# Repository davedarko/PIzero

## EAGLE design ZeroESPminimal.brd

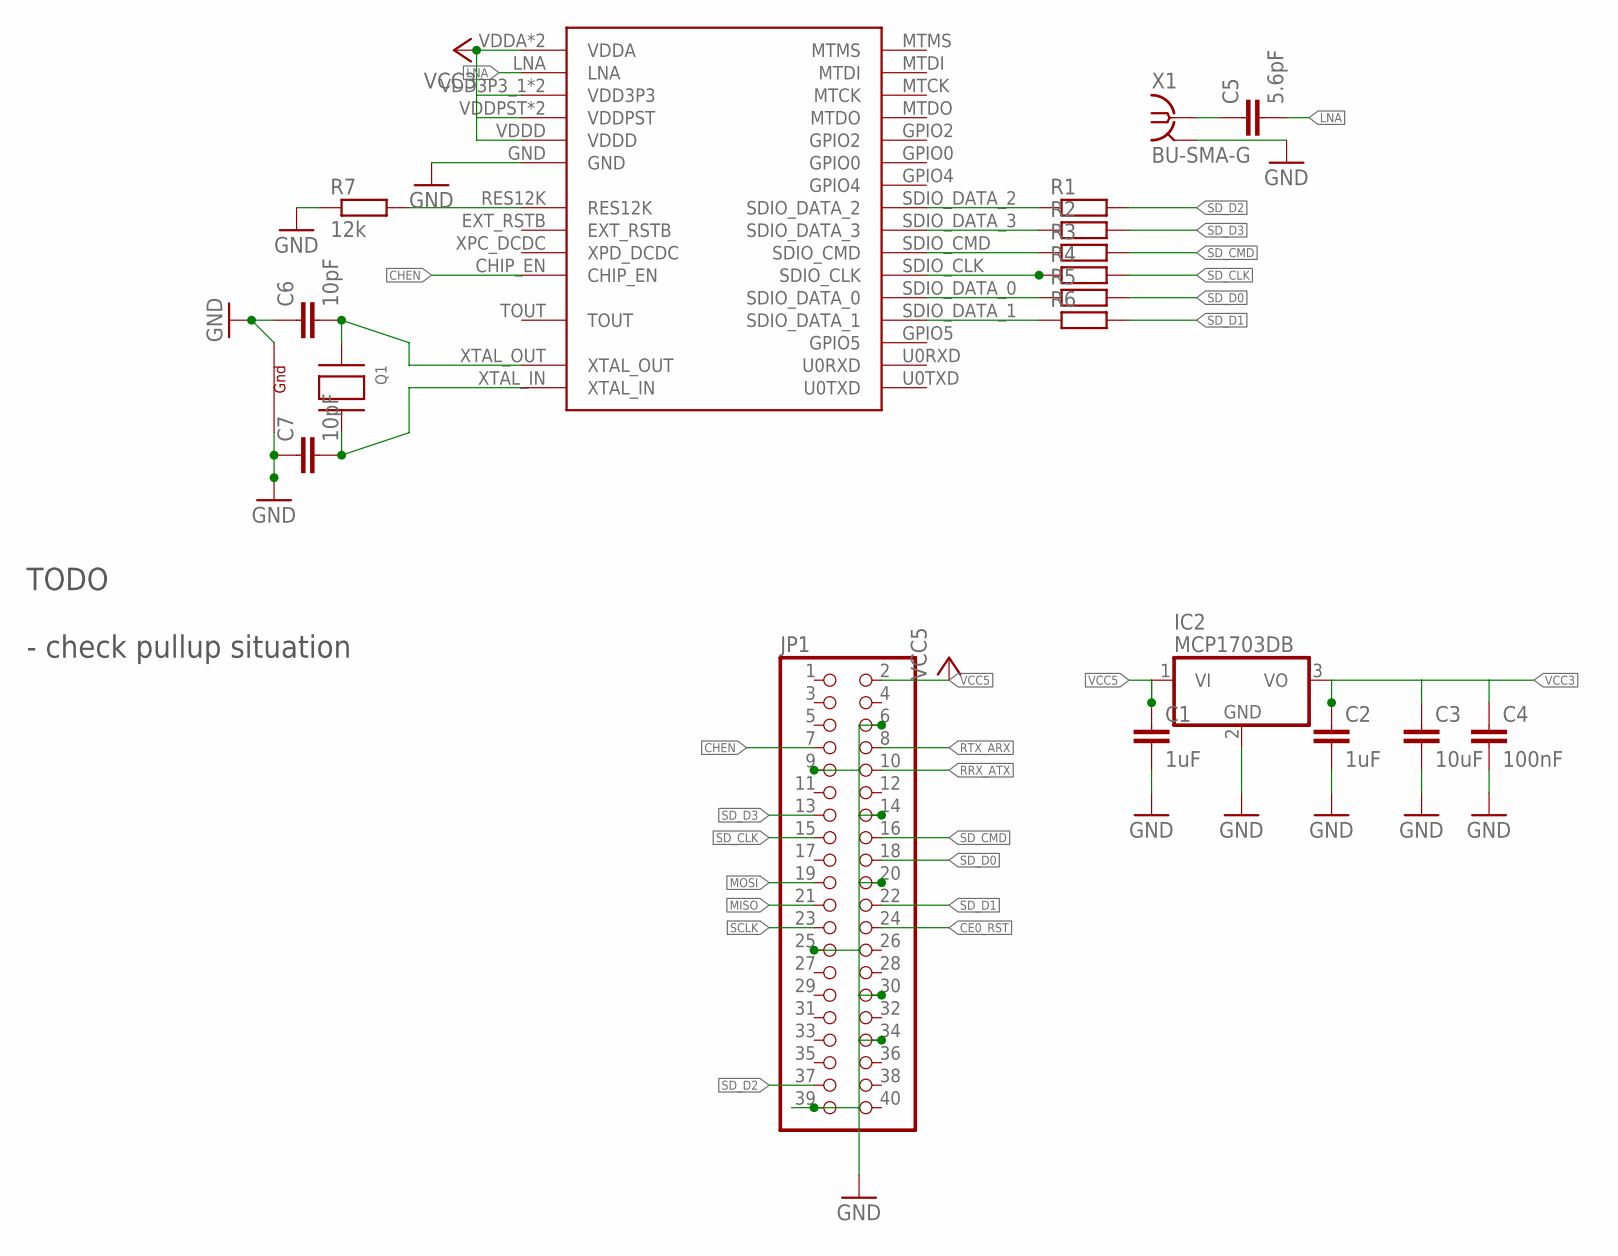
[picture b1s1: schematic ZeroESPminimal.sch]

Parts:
C1, C2: 1uF; C1206
C3: 10uF; C1206
C4: 100nF; C1206
C5: 5.6pF; C0402
C6, C7: 10pF; C0402
IC2: MCP1703DB; SOT223
JP1: PINHD-2X20; 2X20
Q1: XTAL-4-3225; NX3225
R1, R2, R3, R4, R5, R6: R-EU_R0402; R0402
R7: 12k; R0402
U$3: ESP8266EX
X1: BU-SMA-G

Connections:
$N22: R3.1, U$3.SDIO_CMD
$N23: R5.1, U$3.SDIO_DATA_0
$N24: R6.1, U$3.SDIO_DATA_1
CE0_RST: JP1.24
CHEN: JP1.7, U$3.CHIP_EN
GND: C1.2, C2.2, C3.2, C4.2, C6.1, C7.1, IC2.2 (GND), JP1.6, JP1.9, JP1.14, JP1.20, JP1.25, JP1.30, JP1.34, JP1.39, Q1.2 (G2), Q1.4 (G1), R7.1, U$3.GND, X1.2, X1.3 (2), X1.4 (2), X1.5 (2)
LNA: C5.2, U$3.LNA
MISO: JP1.21
MOSI: JP1.19
unnamed: R1.1, U$3.SDIO_DATA_2
unnamed: R2.1, U$3.SDIO_DATA_3
unnamed: C5.1, X1.1
unnamed: R4.1, U$3.SDIO_CLK
unnamed: R7.2, U$3.RES12K
unnamed: C6.2, Q1.1 (X1), U$3.XTAL_OUT
unnamed: C7.2, Q1.3 (X2), U$3.XTAL_IN
RRX_ATX: JP1.10
RTX_ARX: JP1.8
SCLK: JP1.23
SD_CLK: JP1.15, R4.2
SD_CMD: JP1.16, R3.2
SD_D0: JP1.18, R5.2
SD_D1: JP1.22, R6.2
SD_D2: JP1.37, R1.2
SD_D3: JP1.13, R2.2
VCC3: C2.1, C3.1, C4.1, IC2.3 (VO), U$3.VDD3P3_1 (VDD3P3), U$3.VDD3P3_2 (VDD3P3), U$3.VDDA, U$3.VDDA_2 (VDDA), U$3.VDDD, U$3.VDDPST, U$3.VDDPST_2 (VDDPST)
VCC5: C1.1, IC2.1 (VI), JP1.2

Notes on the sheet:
TODO - check pullup situation

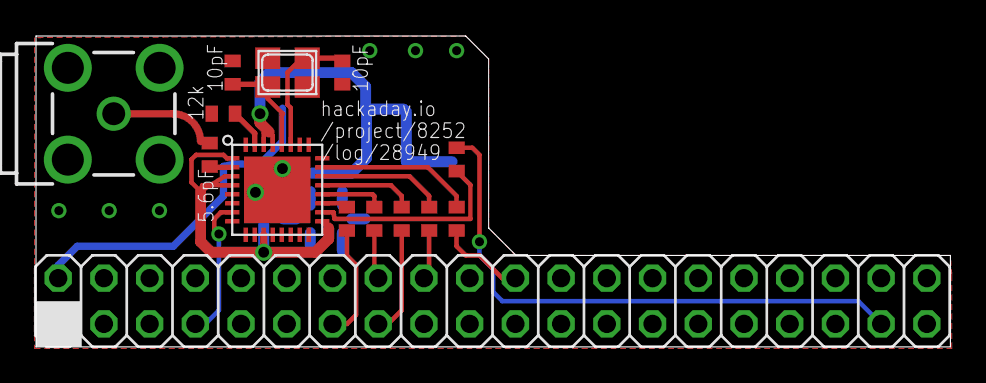
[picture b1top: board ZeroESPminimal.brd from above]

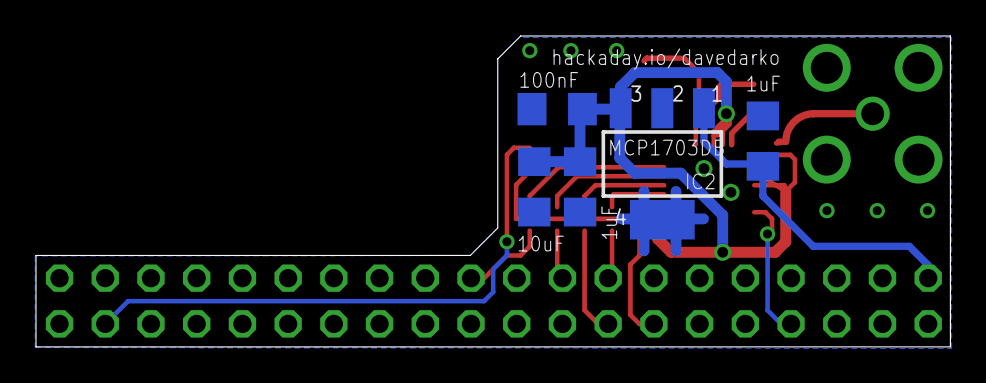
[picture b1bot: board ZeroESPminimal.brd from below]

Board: 2 copper layers, 50.8 x 17.3 mm, 19 parts (5 on the bottom side), 21 nets.

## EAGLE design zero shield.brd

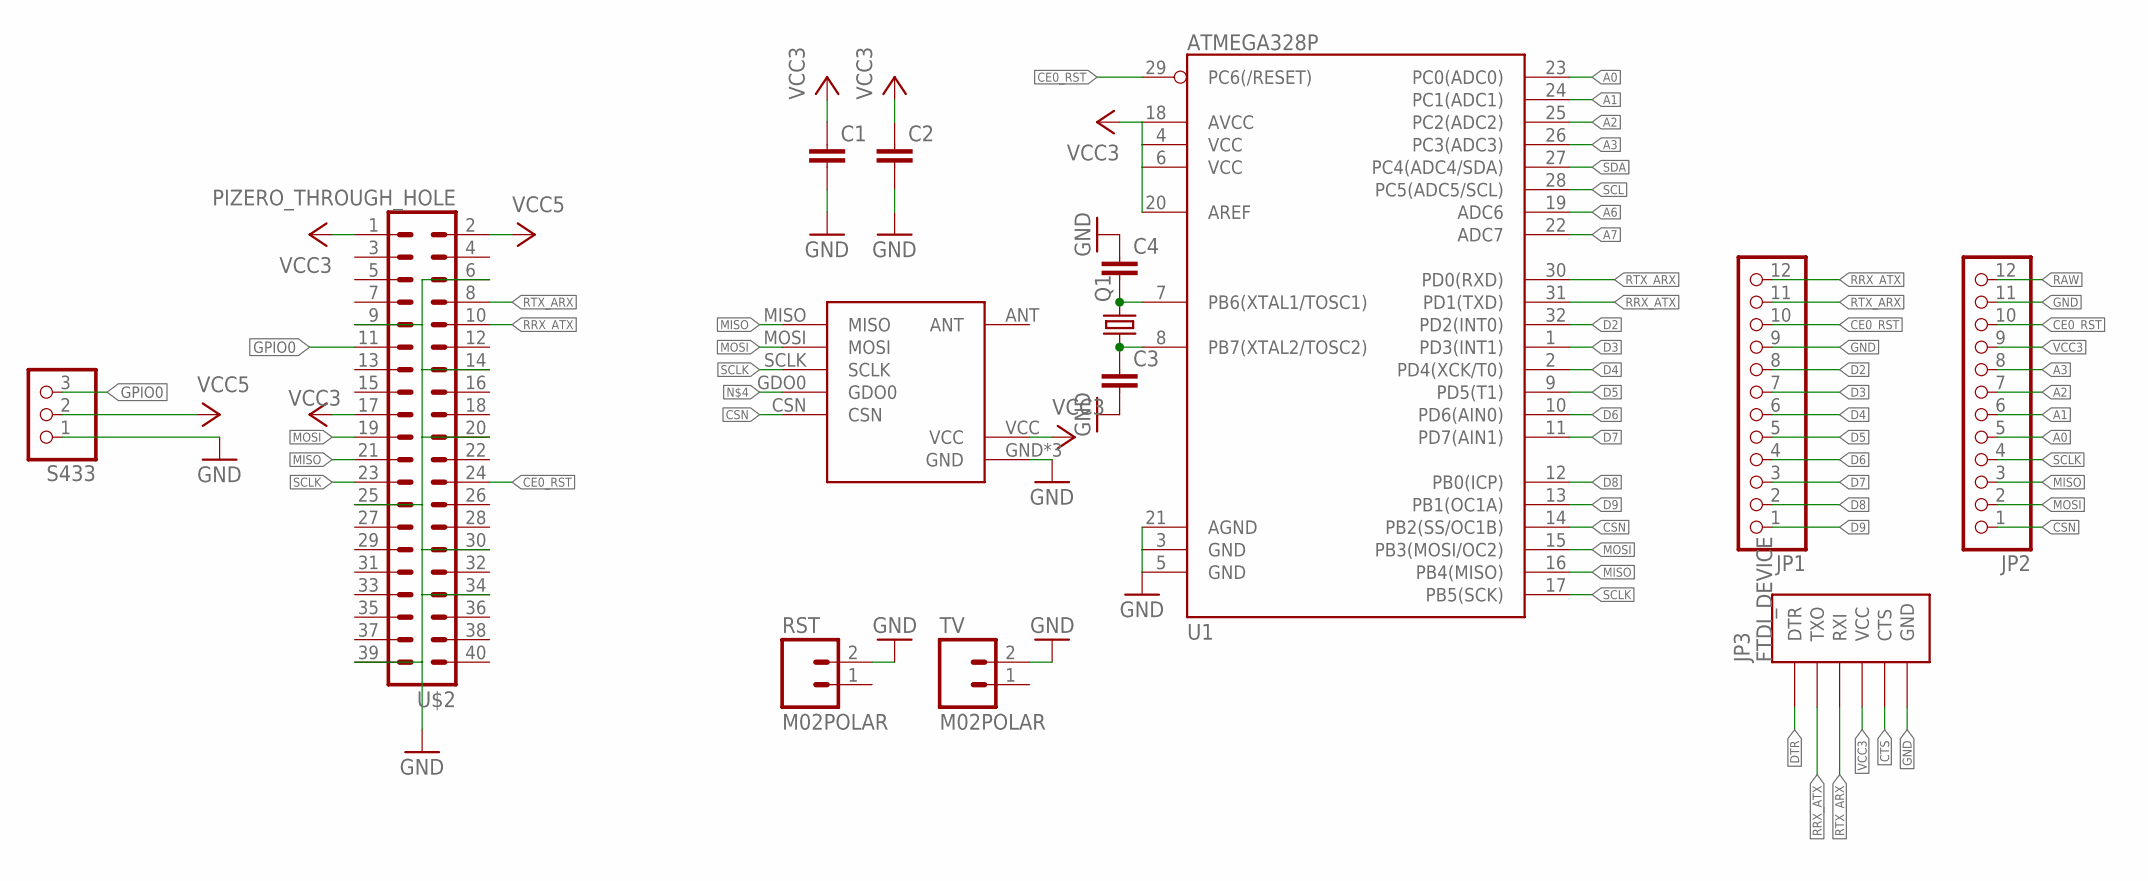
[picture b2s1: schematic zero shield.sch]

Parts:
C1, C2, C3, C4: C-EUC1206K; C1206K
JP1, JP2: PINHD-1X12-CB; 1X12-CB
JP3: FTDI_DEVICE; FTDI_DEVICE_SIDE
Q1: CRYSTALHC49S; HC49/S
RST: M02POLAR; MOLEX-1X2
S433: PINHD-1X3CB; 1X03-CLEANBIG
TV: M02POLAR; MOLEX-1X2
U1: ATMEGA328P; TQFP32-08
U$1: CC1150BOARD
U$2: PIZERO_THROUGH_HOLE; PIZERO_THOUGH_HOLE

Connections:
A0: JP2.5, U1.23 (PC0(ADC0))
A1: JP2.6, U1.24 (PC1(ADC1))
A2: JP2.7, U1.25 (PC2(ADC2))
A3: JP2.8, U1.26 (PC3(ADC3))
A6: U1.19 (ADC6)
A7: U1.22 (ADC7)
CE0_RST: JP1.10, JP2.10, U1.29 (PC6(/RESET)), U$2.24
CSN: JP2.1, U1.14 (PB2(SS/OC1B)), U$1.CSN
CTS: JP3.P$5 (CTS)
D2: JP1.8, U1.32 (PD2(INT0))
D3: JP1.7, U1.1 (PD3(INT1))
D4: JP1.6, U1.2 (PD4(XCK/T0))
D5: JP1.5, U1.9 (PD5(T1))
D6: JP1.4, U1.10 (PD6(AIN0))
D7: JP1.3, U1.11 (PD7(AIN1))
D8: JP1.2, U1.12 (PB0(ICP))
D9: JP1.1, U1.13 (PB1(OC1A))
DTR: JP3.P$1 (DTR)
GND: C1.2, C2.2, C3.2, C4.1, JP1.9, JP2.11, JP3.P$6 (GND), RST.2, S433.1, TV.2, U1.3 (GND), U1.5 (GND), U1.21 (AGND), U$1.GND, U$1.GND2 (GND), U$1.GND3 (GND), U$2.6, U$2.9, U$2.14, U$2.20, U$2.25, U$2.30, U$2.34, U$2.39
GPIO0: S433.3, U$2.11
MISO: JP2.3, U1.16 (PB4(MISO)), U$1.MISO, U$2.21
MOSI: JP2.2, U1.15 (PB3(MOSI/OC2)), U$1.MOSI, U$2.19
unnamed: C4.2, Q1.2, U1.7 (PB6(XTAL1/TOSC1))
unnamed: C3.1, Q1.1, U1.8 (PB7(XTAL2/TOSC2))
RAW: JP2.12
RRX_ATX: JP1.12, JP3.P$2 (TXO), U1.31 (PD1(TXD)), U$2.10
RTX_ARX: JP1.11, JP3.P$3 (RXI), U1.30 (PD0(RXD)), U$2.8
SCL: U1.28 (PC5(ADC5/SCL))
SCLK: JP2.4, U1.17 (PB5(SCK)), U$1.SCLK, U$2.23
SDA: U1.27 (PC4(ADC4/SDA))
VCC3: C1.1, C2.1, JP2.9, JP3.P$4 (VCC), U1.4 (VCC), U1.6 (VCC), U1.18 (AVCC), U1.20 (AREF), U$1.VCC, U$2.1, U$2.17
VCC5: S433.2, U$2.2

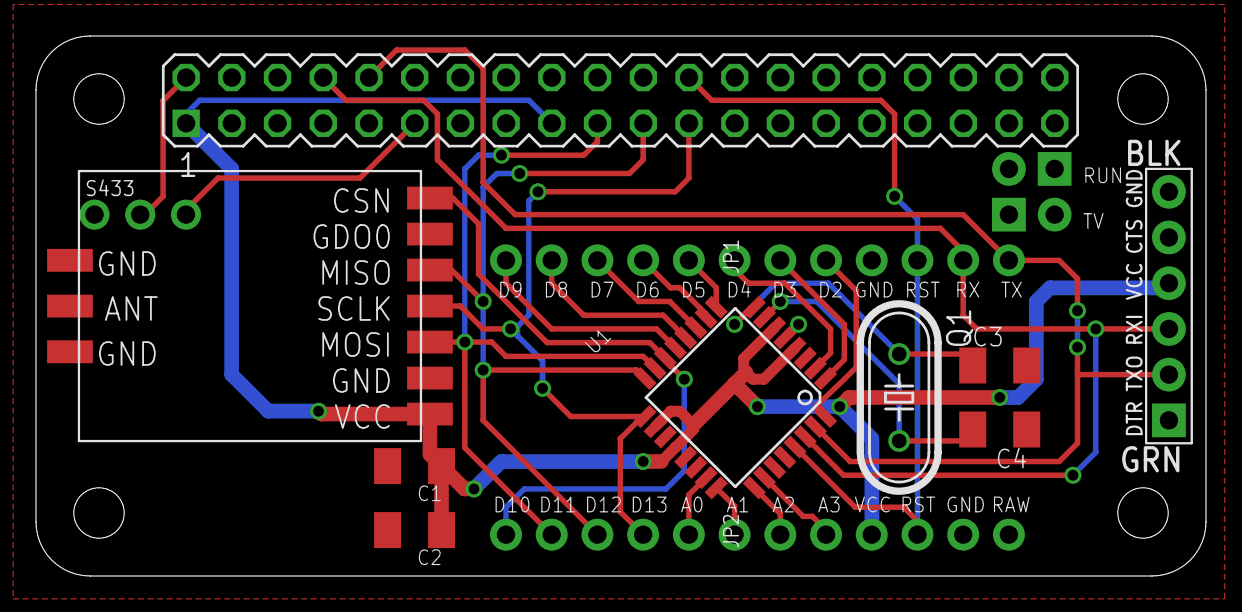
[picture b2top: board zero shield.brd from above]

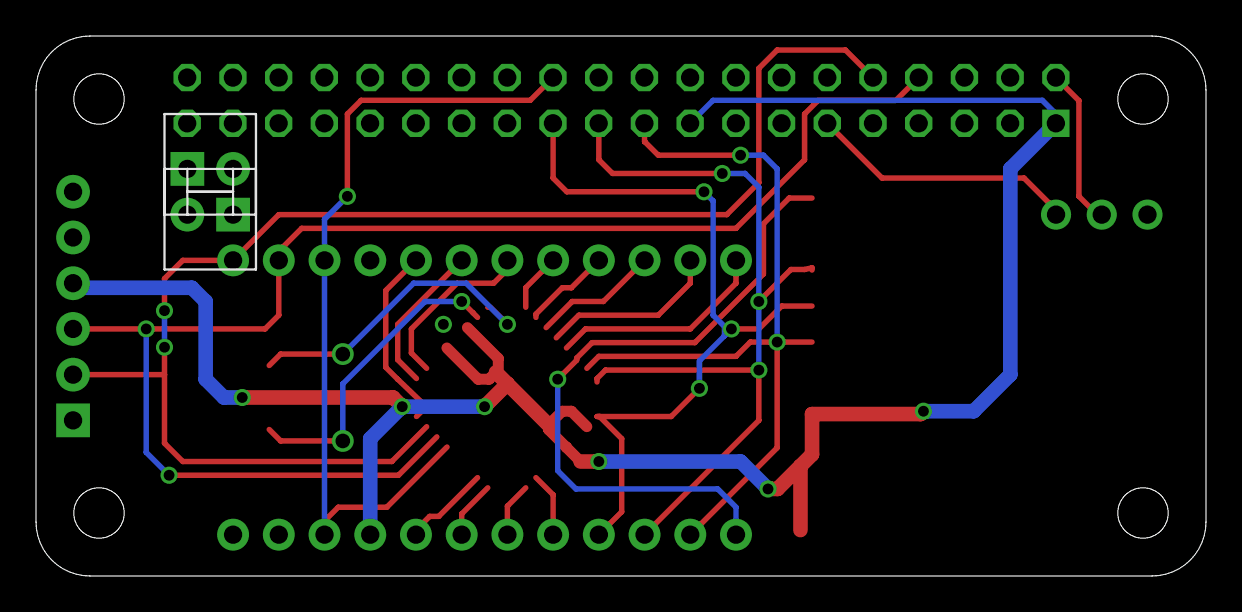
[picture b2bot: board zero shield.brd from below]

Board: 2 copper layers, 65.0 x 30.0 mm, 14 parts (2 on the bottom side), 25 nets.

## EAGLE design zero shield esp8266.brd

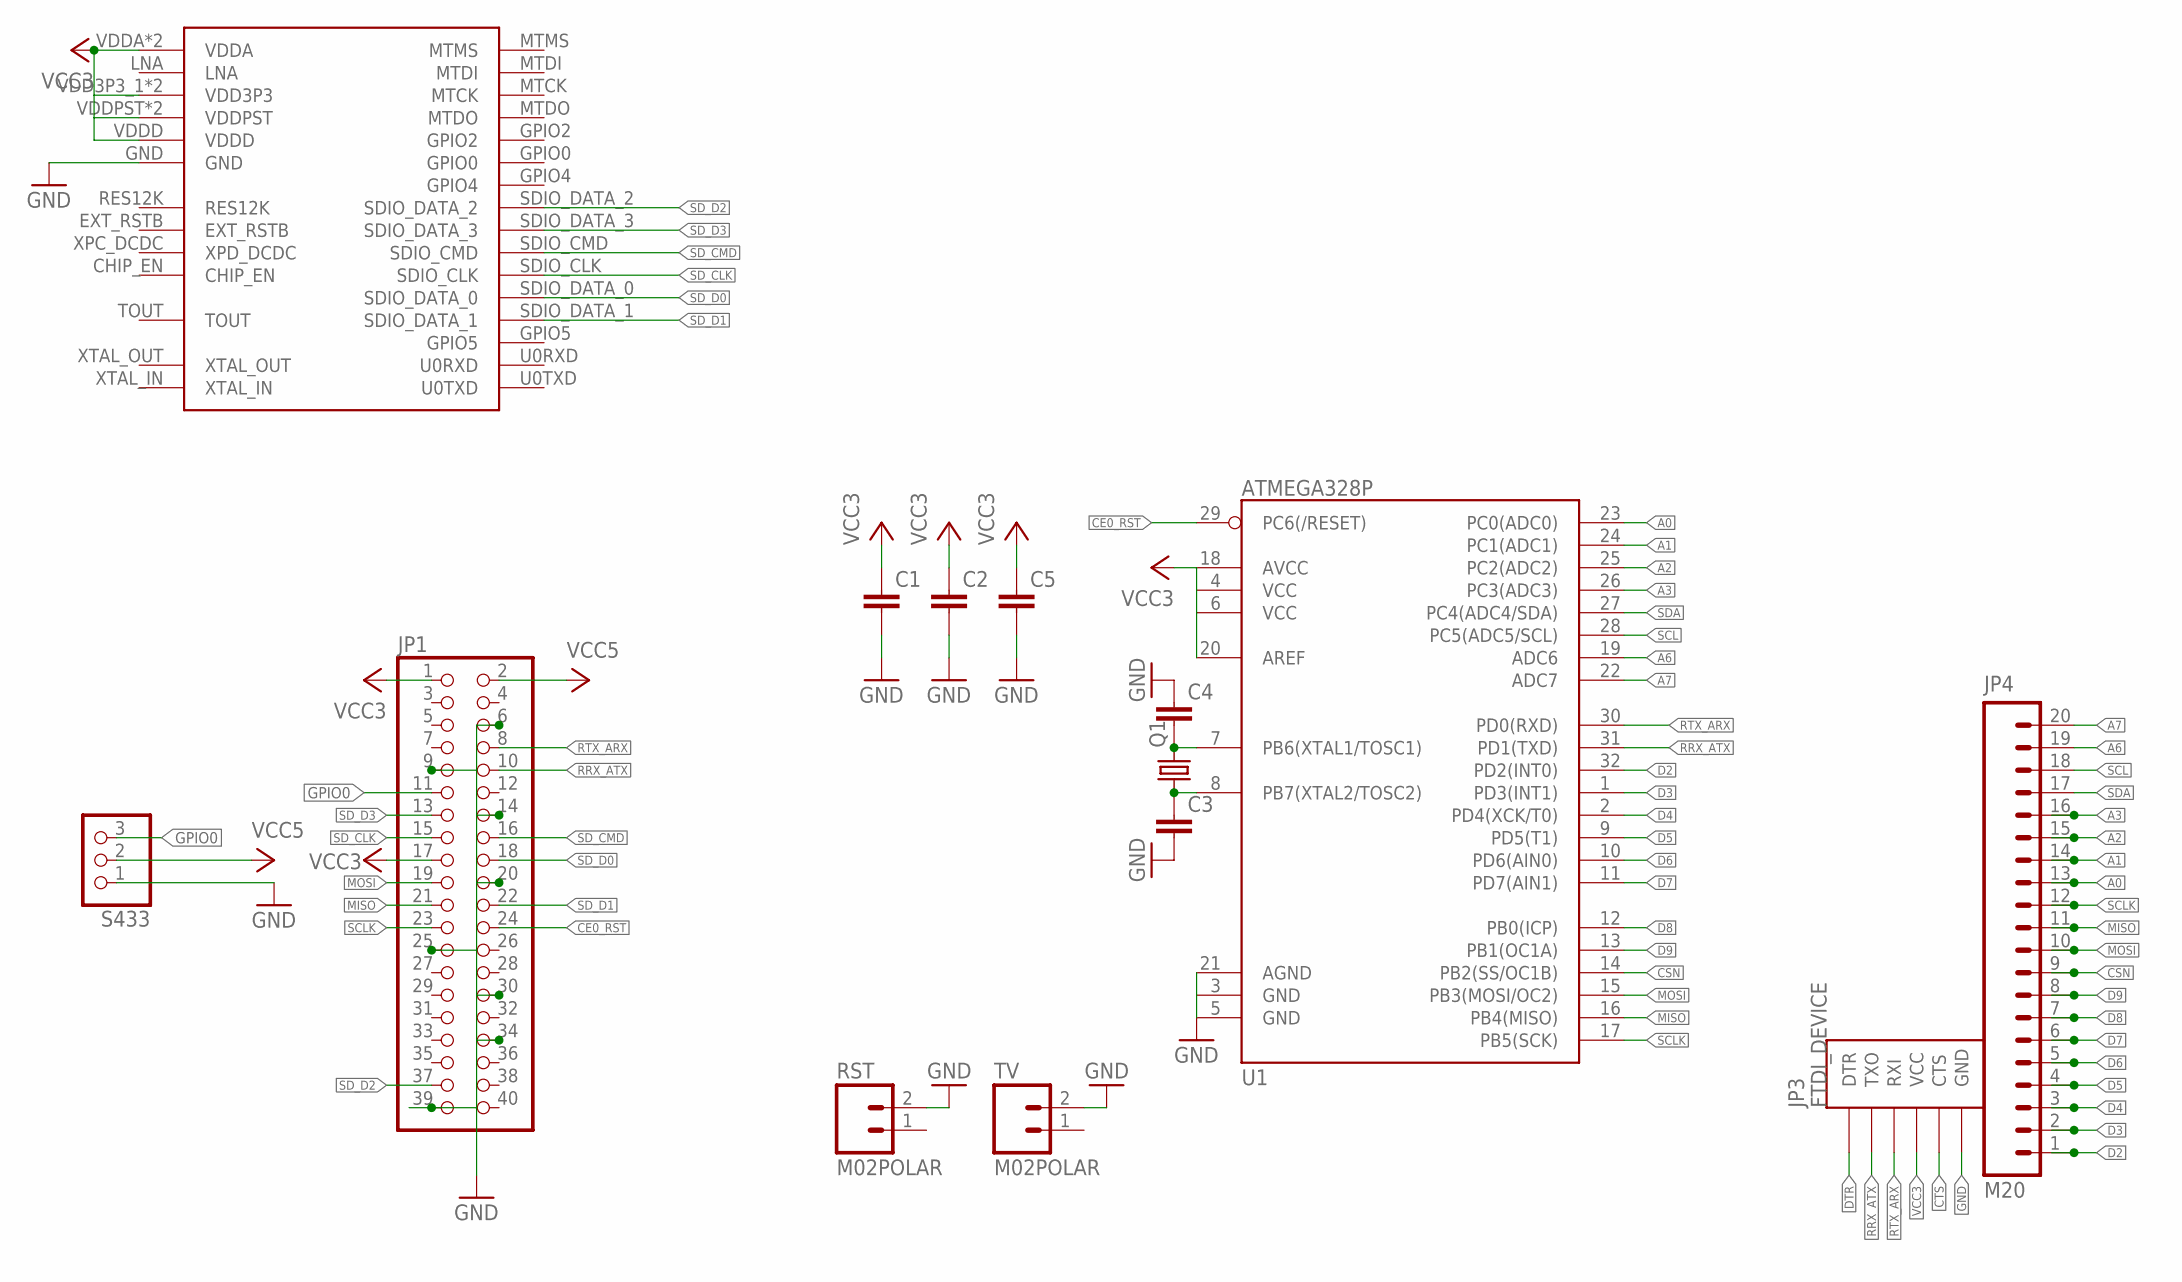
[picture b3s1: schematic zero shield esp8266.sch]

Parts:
C1, C2, C3, C4, C5: C-EUC1206K; C1206K
JP1: PINHD-2X20; 2X20
JP3: FTDI_DEVICE; FTDI_DEVICE_SIDE
JP4: M20; 1X20
Q1: CRYSTALHC49S; HC49/S
RST: M02POLAR; MOLEX-1X2
S433: PINHD-1X3CB; 1X03-CLEANBIG
TV: M02POLAR; MOLEX-1X2
U1: ATMEGA328P; TQFP32-08
U$3: ESP8266EX

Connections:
A0: JP4.13, U1.23 (PC0(ADC0))
A1: JP4.14, U1.24 (PC1(ADC1))
A2: JP4.15, U1.25 (PC2(ADC2))
A3: JP4.16, U1.26 (PC3(ADC3))
A6: JP4.19, U1.19 (ADC6)
A7: JP4.20, U1.22 (ADC7)
CE0_RST: JP1.24, U1.29 (PC6(/RESET))
CSN: JP4.9, U1.14 (PB2(SS/OC1B))
CTS: JP3.P$5 (CTS)
D2: JP4.1, U1.32 (PD2(INT0))
D3: JP4.2, U1.1 (PD3(INT1))
D4: JP4.3, U1.2 (PD4(XCK/T0))
D5: JP4.4, U1.9 (PD5(T1))
D6: JP4.5, U1.10 (PD6(AIN0))
D7: JP4.6, U1.11 (PD7(AIN1))
D8: JP4.7, U1.12 (PB0(ICP))
D9: JP4.8, U1.13 (PB1(OC1A))
DTR: JP3.P$1 (DTR)
GND: C1.2, C2.2, C3.2, C4.1, C5.2, JP1.6, JP1.9, JP1.14, JP1.20, JP1.25, JP1.30, JP1.34, JP1.39, JP3.P$6 (GND), RST.2, S433.1, TV.2, U1.3 (GND), U1.5 (GND), U1.21 (AGND), U$3.GND
GPIO0: JP1.11, S433.3
MISO: JP1.21, JP4.11, U1.16 (PB4(MISO))
MOSI: JP1.19, JP4.10, U1.15 (PB3(MOSI/OC2))
unnamed: C4.2, Q1.2, U1.7 (PB6(XTAL1/TOSC1))
unnamed: C3.1, Q1.1, U1.8 (PB7(XTAL2/TOSC2))
RRX_ATX: JP1.10, JP3.P$2 (TXO), U1.31 (PD1(TXD))
RTX_ARX: JP1.8, JP3.P$3 (RXI), U1.30 (PD0(RXD))
SCL: JP4.18, U1.28 (PC5(ADC5/SCL))
SCLK: JP1.23, JP4.12, U1.17 (PB5(SCK))
SDA: JP4.17, U1.27 (PC4(ADC4/SDA))
SD_CLK: JP1.15, U$3.SDIO_CLK
SD_CMD: JP1.16, U$3.SDIO_CMD
SD_D0: JP1.18, U$3.SDIO_DATA_0
SD_D1: JP1.22, U$3.SDIO_DATA_1
SD_D2: JP1.37, U$3.SDIO_DATA_2
SD_D3: JP1.13, U$3.SDIO_DATA_3
VCC3: C1.1, C2.1, JP1.1, JP1.17, JP3.P$4 (VCC), U1.4 (VCC), U1.6 (VCC), U1.18 (AVCC), U1.20 (AREF), U$3.VDD3P3_1 (VDD3P3), U$3.VDD3P3_2 (VDD3P3), U$3.VDDA, U$3.VDDA_2 (VDDA), U$3.VDDD, U$3.VDDPST, U$3.VDDPST_2 (VDDPST)
VCC5: C5.1, JP1.2, S433.2

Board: 2 copper layers, 14 parts (2 on the bottom side), 35 nets, no tracks yet.

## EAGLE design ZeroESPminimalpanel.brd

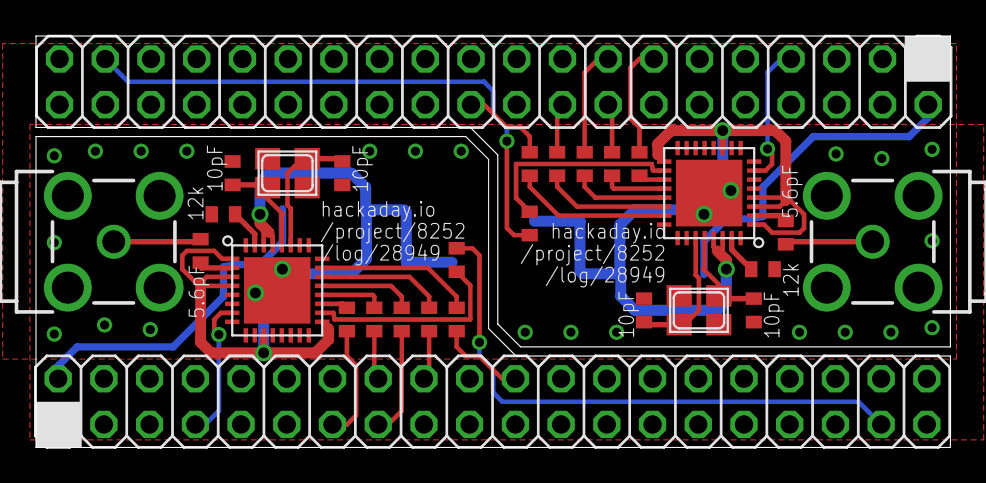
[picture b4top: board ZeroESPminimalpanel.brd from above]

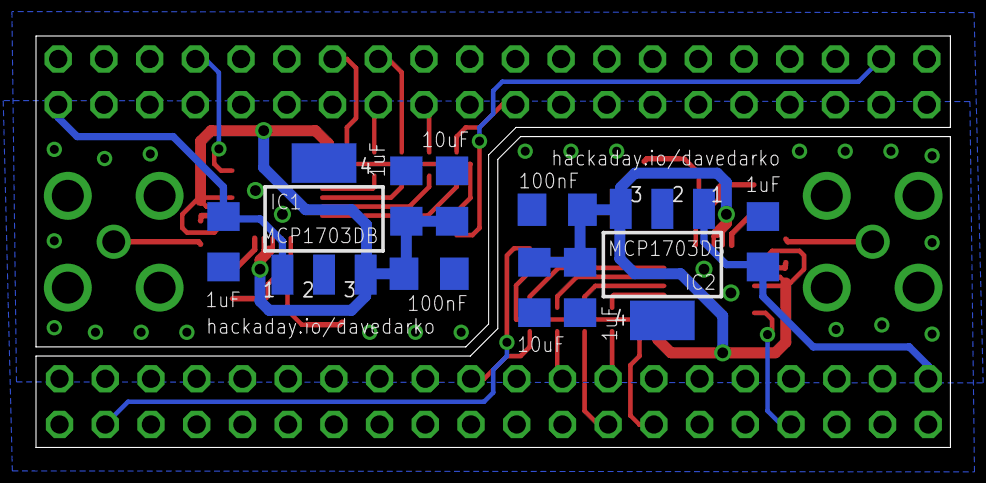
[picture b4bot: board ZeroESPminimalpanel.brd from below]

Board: 2 copper layers, 50.8 x 22.9 mm, 38 parts (10 on the bottom side), 42 nets.

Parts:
C1, C2, C8, C9: 1uF; C1206
C3, C10: 10uF; C1206
C4, C11: 100nF; C1206
C5, C12: 5.6pF; C0402
C6, C7, C13, C14: 10pF; C0402
IC1, IC2: MCP1703DB; SOT223
JP1, JP2: 2X20
Q1, Q2: NX3225
R1, R2, R3, R4, R5, R6, R8, R9, R10, R11, R12, R13: R0402
R7, R14: 12k; R0402
U$1, U$3: ESP8266EX
X1, X2: BU-SMA-G

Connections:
$N1: R11.1, U$1.SDIO_CMD
$N2: R12.1, U$1.SDIO_DATA_0
$N3: R13.1, U$1.SDIO_DATA_1
$N22: R3.1, U$3.SDIO_CMD
$N23: R5.1, U$3.SDIO_DATA_0
$N24: R6.1, U$3.SDIO_DATA_1
CHEN: JP1.7, U$3.CHIP_EN
CHEN1: JP2.7, U$1.CHIP_EN
GND: C1.2, C2.2, C3.2, C4.2, C6.1, C7.1, IC2.2, JP1.6, JP1.9, JP1.14, JP1.20, JP1.25, JP1.30, JP1.34, JP1.39, Q1.2, Q1.4, R7.1, U$3.GND, X1.2, X1.3, X1.4, X1.5
GND1: C8.2, C9.2, C10.2, C11.2, C13.1, C14.1, IC1.2, JP2.6, JP2.9, JP2.14, JP2.20, JP2.25, JP2.30, JP2.34, JP2.39, Q2.2, Q2.4, R14.1, U$1.GND, X2.2, X2.3, X2.4, X2.5
LNA: C5.2, U$3.LNA
LNA1: C12.2, U$1.LNA
unnamed: R1.1, U$3.SDIO_DATA_2
unnamed: R2.1, U$3.SDIO_DATA_3
unnamed: C5.1, X1.1
unnamed: R4.1, U$3.SDIO_CLK
unnamed: R7.2, U$3.RES12K
unnamed: R8.1, U$1.SDIO_CLK
unnamed: C6.2, Q1.1, U$3.XTAL_OUT
unnamed: R9.1, U$1.SDIO_DATA_2
unnamed: C7.2, Q1.3, U$3.XTAL_IN
unnamed: R10.1, U$1.SDIO_DATA_3
unnamed: C12.1, X2.1
unnamed: R14.2, U$1.RES12K
unnamed: C13.2, Q2.1, U$1.XTAL_OUT
unnamed: C14.2, Q2.3, U$1.XTAL_IN
SD_CLK: JP1.15, R4.2
SD_CLK1: JP2.15, R8.2
SD_CMD: JP1.16, R3.2
SD_CMD1: JP2.16, R11.2
SD_D0: JP1.18, R5.2
SD_D1: JP1.22, R6.2
SD_D2: JP1.37, R1.2
SD_D3: JP1.13, R2.2
SD_D4: JP2.18, R12.2
SD_D5: JP2.22, R13.2
SD_D6: JP2.37, R9.2
SD_D7: JP2.13, R10.2
VCC1: C9.1, C10.1, C11.1, IC1.3, U$1.VDD3P3_1, U$1.VDD3P3_2, U$1.VDDA, U$1.VDDA_2, U$1.VDDD, U$1.VDDPST, U$1.VDDPST_2
VCC2: C8.1, IC1.1, JP2.2
VCC3: C2.1, C3.1, C4.1, IC2.3, U$3.VDD3P3_1, U$3.VDD3P3_2, U$3.VDDA, U$3.VDDA_2, U$3.VDDD, U$3.VDDPST, U$3.VDDPST_2
VCC5: C1.1, IC2.1, JP1.2

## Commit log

2015-12-12 First Draft
2015-12-12 minor changes
2015-12-12 connected ground pad of leo

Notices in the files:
parts and their libraries:
SparkFun-Connectors: Licensing: Creative Commons ShareAlike 4.0 International - https://creativecommons.org/licenses/by-sa/4.0
